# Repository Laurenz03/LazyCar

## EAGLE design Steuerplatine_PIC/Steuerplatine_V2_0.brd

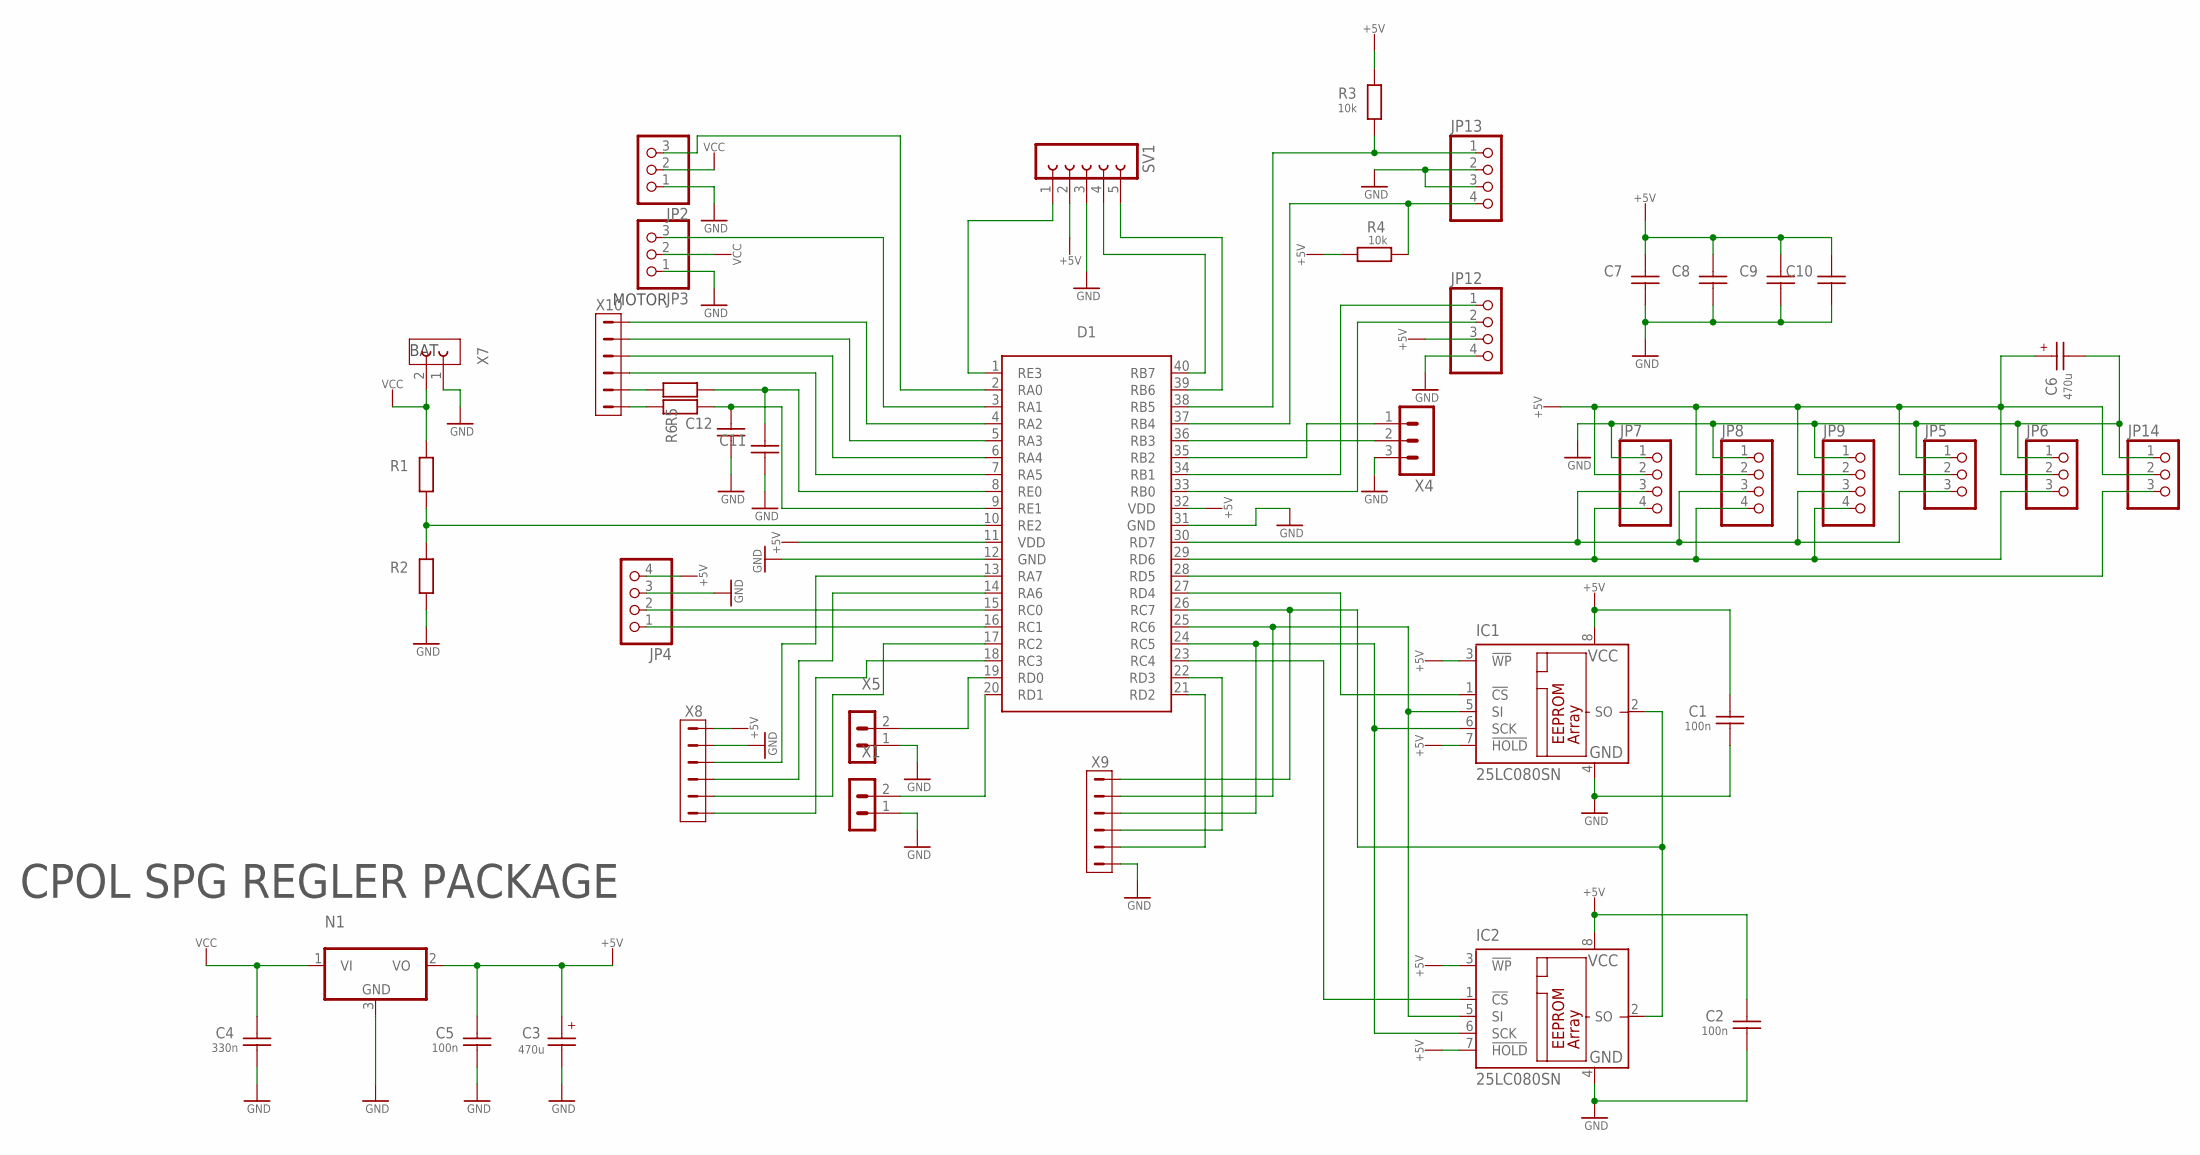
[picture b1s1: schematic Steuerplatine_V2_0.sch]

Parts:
C1, C2: 100n; C0603
C3, C6: 470u; E5-10,5
C4: 330n; C1206
C5: 100n; C1206
C7, C8, C9, C10, C11, C12: C-V_C1206; C1206
D1: EVAL_BRD_PIC18F46K421; EVAL_BRD_PIC18F46K42
IC1, IC2: 25LC080SN; SO-08
JP2, JP3, JP5, JP6, JP14: PINHD-1X3; 1X03
JP4, JP7, JP8, JP9, JP12, JP13: PINHD-1X4; 1X04
N1: 7805DT; TO252
R1, R2, R5, R6: R-V_R1206; R1206
R3, R4: 10k; R1206
SV1: FE05-1
X1, X5: M02; 02P
X4: MA03-1
X7: PRINTKLEMME2_PHOENIX_MPT; PHOENIX_MPT
X8, X9, X10: MA06-1_; MA06-1

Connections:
+5V: C1.1, C2.1, C3.+, C5.1, C6.+, C7.1, C8.1, C9.1, C10.1, D1.11 (VDD), D1.32 (VDD), IC1.3 (!WP), IC1.7 (!HOLD), IC1.8 (VCC), IC2.3 (!WP), IC2.7 (!HOLD), IC2.8 (VCC), JP4.4, JP5.2, JP6.2, JP7.2, JP8.2, JP9.2, JP12.3, JP14.2, N1.2 (VO), R3.2, R4.1, SV1.2, X8.6
GND: C1.2, C2.2, C3.-, C4.2, C5.2, C6.-, C7.2, C8.2, C9.2, C10.2, C11.2, C12.2, D1.12 (GND), D1.31 (GND), IC1.4 (GND), IC2.4 (GND), JP2.1, JP3.1, JP4.3, JP5.1, JP6.1, JP7.1, JP8.1, JP9.1, JP12.4, JP13.2, JP13.3, JP14.1, N1.3 (GND), R2.1, SV1.3, X1.1, X4.3, X5.1, X7.1, X8.5, X9.1
unnamed: D1.10 (RE2), R1.1, R2.2
unnamed: D1.24 (RC5), IC1.6 (SCK), IC2.6 (SCK), X9.4
unnamed: C12.1, D1.9 (RE1), R6.1
unnamed: C11.1, D1.8 (RE0), R5.1
unnamed: D1.7 (RA5), X10.3
unnamed: D1.6 (RA4), X10.4
unnamed: D1.5 (RA3), X10.5
unnamed: D1.23 (RC4), IC2.1 (!CS)
unnamed: D1.4 (RA2), X10.6
unnamed: D1.2 (RA0), JP2.3
unnamed: D1.3 (RA1), JP3.3
unnamed: D1.29 (RD6), JP6.3, JP7.4, JP8.4, JP9.4
unnamed: D1.33 (RB0), JP12.2
unnamed: D1.30 (RD7), JP5.3, JP7.3, JP8.3, JP9.3
unnamed: D1.21 (RD2), X9.2
unnamed: D1.28 (RD5), JP14.3
unnamed: D1.26 (RC7), IC1.2 (SO), IC2.2 (SO), X9.6
unnamed: D1.27 (RD4), IC1.1 (!CS)
unnamed: D1.16 (RC1), JP4.1
unnamed: D1.15 (RC0), JP4.2
unnamed: D1.25 (RC6), IC1.5 (SI), IC2.5 (SI), X9.5
unnamed: D1.22 (RD3), X9.3
unnamed: D1.13 (RA7), X8.4
unnamed: D1.36 (RB3), X4.2
unnamed: D1.35 (RB2), X4.1
unnamed: D1.14 (RA6), X8.3
unnamed: D1.34 (RB1), JP12.1
unnamed: R5.2, X10.2
unnamed: D1.18 (RC3), X8.1
unnamed: D1.38 (RB5), JP13.1, R3.1
unnamed: D1.37 (RB4), JP13.4, R4.2
unnamed: D1.17 (RC2), X8.2
unnamed: D1.40 (RB7), SV1.4
unnamed: D1.39 (RB6), SV1.5
unnamed: D1.1 (RE3), SV1.1
unnamed: D1.19 (RD0), X5.2
unnamed: D1.20 (RD1), X1.2
unnamed: R6.2, X10.1
VCC: C4.1, JP2.2, JP3.2, N1.1 (VI), R1.2, X7.2

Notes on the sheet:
BAT
MOTOR
CPOL SPG REGLER PACKAGE

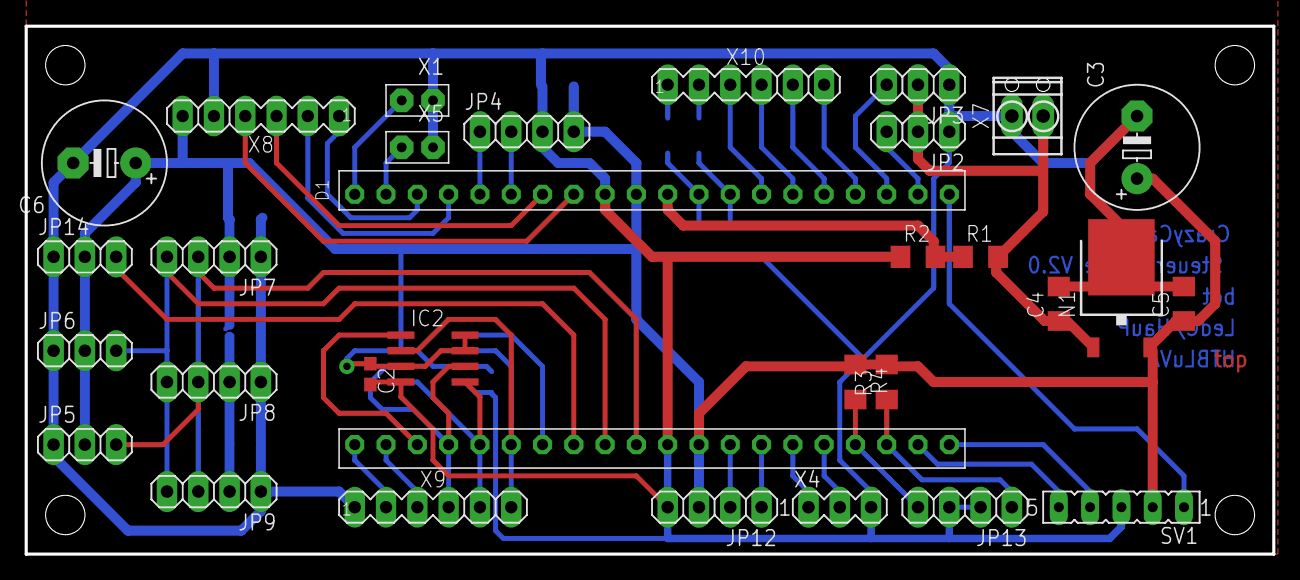
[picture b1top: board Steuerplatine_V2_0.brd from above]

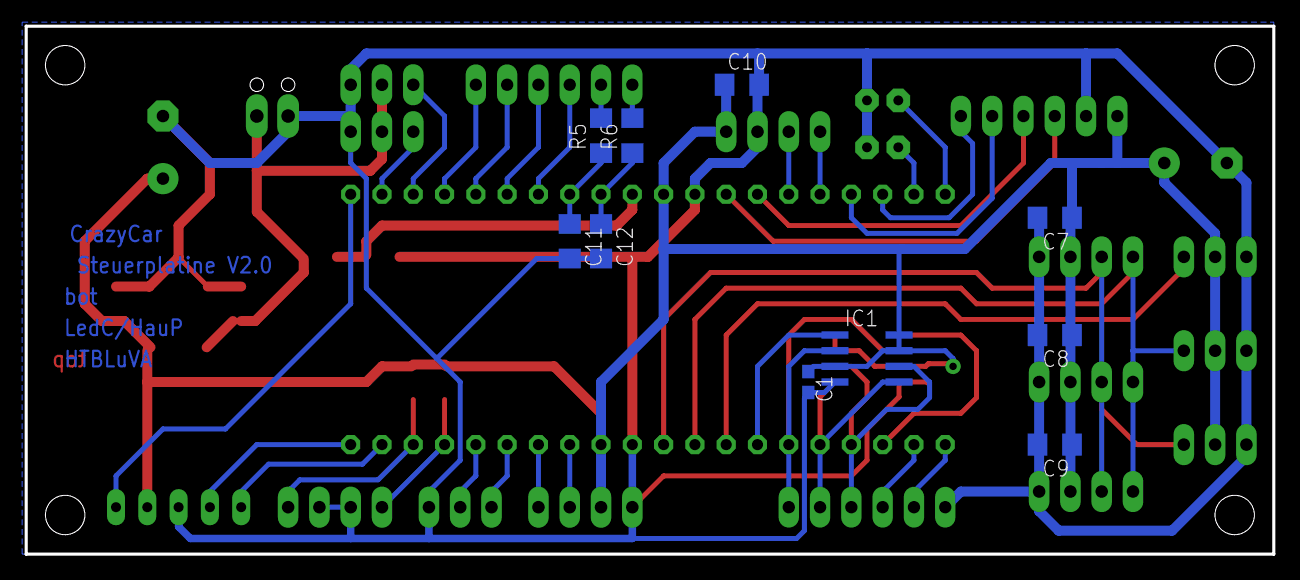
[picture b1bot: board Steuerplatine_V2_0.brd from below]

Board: 2 copper layers, 101.3 x 42.9 mm, 41 parts (10 on the bottom side), 41 nets.

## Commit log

2020-09-15 Create fff
